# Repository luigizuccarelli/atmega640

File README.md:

# atmega640 iot-controller

## Overview 

The software used in this project cover
- xl335 accelerometer
- ds18b20 digital temperature sensor

It ouptuts data to the serial usb /dev/ttyUSB0 (which can be configured)
The main loop waits for a char from the serial port and then takes a mesurement of both sensors

## Interface
As mentioned all connectovity is from and to the serial usb device
This gives a good layer of abstraction (not dependant on specific pinouts)
The controller is an omega onion + written in golang
Data transferred for the temperature probe and accelerometer are int values, converiosn to float takes place at the golang omega contoller

## AVR fuses
Internal clock divide by 8 startup time set to max , spi and jtag enable, bootsize set to 00

```bash
-U lfuse:w:0x62:m -U hfuse:w:0x99:m -U efuse:w:0xff:m
```

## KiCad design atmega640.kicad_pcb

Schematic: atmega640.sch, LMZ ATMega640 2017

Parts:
C1, C2: 22pf; C_0805_HandSoldering
C3, C4, C5, C6, C7: 100nf; C_0805_HandSoldering
J1: CONN_02X03; Pin_Header_Straight_2x03_Pitch2.54mm
J2, J3: CONN_02X20; Pin_Header_Straight_2x20_Pitch2.54mm
R1: 4k7; R_0805_HandSoldering
U1: ATMEGA640-16AU; TQFP-100_14x14mm_Pitch0.5mm
Y1: 16MHz; Crystal_SMD_7050-4pin_7.0x5.0mm

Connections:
+5VD: C3.1, C4.1, C5.1, C6.1, C7.1, J1.2, J2.34, J2.36, J2.38, J2.40, R1.1, U1.10 (VCC), U1.31 (VCC), U1.61 (VCC), U1.80 (VCC), U1.100 (AVCC)
/ADC0: J2.1, U1.97 ((ADC0)PF0)
/ADC1: J2.3, U1.96 ((ADC1)PF1)
/ADC2: J2.5, U1.95 ((ADC2)PF2)
/ADC3: J2.7, U1.94 ((ADC3)PF3)
/ADC4: J2.9, U1.93 ((TCK/ADC4)PF4)
/ADC5: J2.11, U1.92 ((TMS/ADC5)PF5)
/ADC6: J2.13, U1.91 ((TD0/ADC6)PF6)
/ADC7: J2.15, U1.90 ((TDI/ADC7)PF7)
/ADC8: J2.17, U1.89 (PK0(ADC8/PCINT16))
/ADC9: J2.19, U1.88 (PK1(ADC9/PCINT17))
/ADC10: J2.21, U1.87 (PK2(ADC10/PCINT18))
/ADC11: J2.23, U1.86 (PK3(ADC11/PCINT19))
/ADC12: J2.25, U1.85 (PK4(ADC12/PCINT20))
/ADC13: J2.27, U1.84 (PK5(ADC13/PCINT21))
/ADC14: J2.29, U1.83 (PK6(ADC14/PCINT22))
/ADC15: J2.31, U1.82 (PK7(ADC15/PCINT23))
/AREF: J3.18, U1.98 (AREF)
/PA0: J2.2, U1.78 ((AD0)PA0)
/PA1: J2.4, U1.77 ((AD1)PA1)
/PA2: J2.6, U1.76 ((AD2)PA2)
/PA3: J2.8, U1.75 ((AD3)PA3)
/PA4: J2.10, U1.74 ((AD4)PA4)
/PA5: J2.12, U1.73 ((AD5)PA5)
/PA6: J2.14, U1.72 ((AD6)PA6)
/PA7: J2.16, U1.71 ((AD7)PA7)
/PC0: J2.18, U1.60 ((A15)PC7)
/PC1: J2.20, U1.59 ((A14)PC6)
/PC2: J2.22, U1.58 ((A13)PC5)
/PC3: J2.24, U1.57 ((A12)PC4)
/PC4: J2.26, U1.56 ((A11)PC3)
/PC5: J2.28, U1.55 ((A10)PC2)
/PC6: J2.30, U1.54 ((A9)PC1)
/PC7: J2.32, U1.53 ((A8)PC0)
/PE0: J3.1, U1.2 ((PCINT8/RXD0)PE0)
/PE1: J3.3, U1.3 ((TXD0)PE1)
/PE2: J3.5, U1.4 ((XCK0/AIN0)PE2)
/PE3: J3.7, U1.5 ((OC3A/AIN1)PE3)
/PE4: J3.9, U1.6 ((OC3B/INT4)PE4)
/PE5: J3.11, U1.7 ((OC3C/INT5)PE5)
/PE6: J3.13, U1.8 ((T3/INT6)PE6)
/PE7: J3.15, U1.9 ((CLKO/ICP3/INT7)PE7)
/PH0: J3.2, U1.12 (PH0(RXD2))
/PH1: J3.4, U1.13 (PH1(TXD2))
/PH2: J3.6, U1.14 (PH2(XCK2))
/PH3: J3.8, U1.15 (PH3(OC4A))
/PH4: J3.10, U1.16 (PH4(OC4B))
/PH5: J3.12, U1.17 (PH5(OC4C))
/PH6: J3.14, U1.18 (PH6(OC2B))
/PH7: J3.16, U1.27 (PH7(T4))
GND: C1.2, C2.2, C3.2, C4.2, C5.2, C6.2, C7.2, J1.6, J2.33, J2.35, J2.37, J2.39, U1.11 (GND), U1.32 (GND), U1.62 (GND), U1.81 (GND), U1.99 (GND)
unnamed: C1.1, U1.33 (XTAL2), Y1.1
unnamed: C2.1, U1.34 (XTAL1), Y1.3
unnamed: J1.1, U1.22 ((PCINT3/MISO)PB3)
unnamed: J1.3, U1.20 ((PCINT1/SCK)PB1)
unnamed: J1.4, U1.21 ((PCINT2/MOSI)PB2)
unnamed: J1.5, R1.2, U1.30 (~RESET)

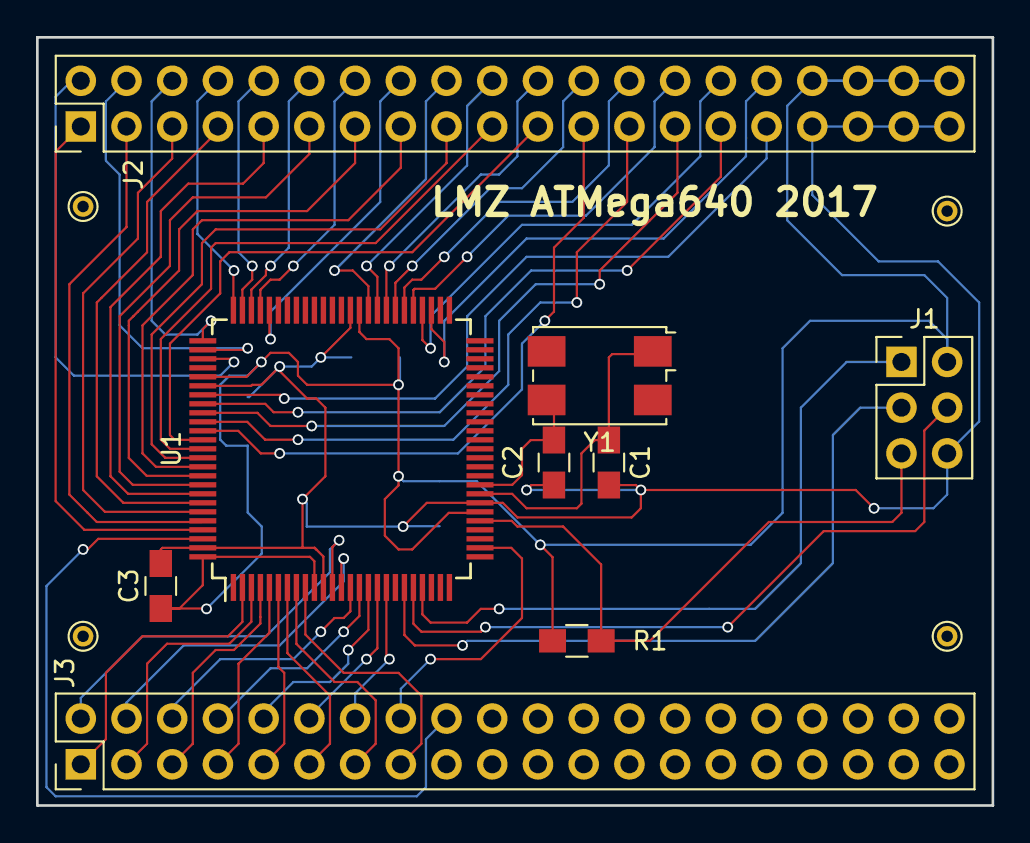
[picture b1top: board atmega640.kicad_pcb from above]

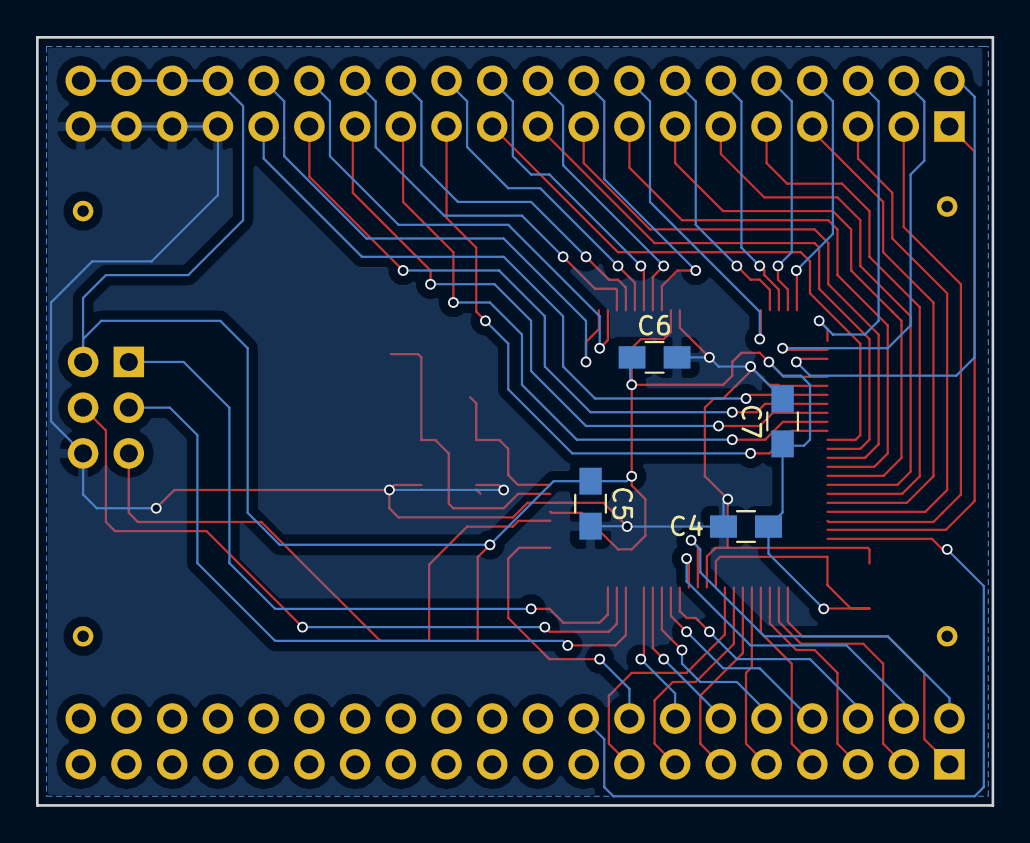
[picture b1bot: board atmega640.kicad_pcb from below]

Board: 2 copper layers, 53.1 x 42.7 mm, 13 parts (4 on the bottom side), 57 nets.

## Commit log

2021-03-28 Initial commit
    Why:
    * IOT controller for gmd
    Solution:
    * Kicad design files and c code for sensors
    Task link:
    * NA
2021-03-28 Updated README
    Why:
    * IOT controller for gmd
    Solution:
    * Kicad design files and c code for sensors
    Task link:
    * NA
